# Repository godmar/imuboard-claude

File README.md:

# LSM6DSV32X Breakout

A minimal breakout for the ST **LSM6DSV32X** 6-axis IMU (±32 g accel, ±4000 dps gyro).
The circuit follows the mode 1 connection diagram in ST's datasheet (DS13511, Figure 28,
section 7.1).

| | |
|---|---|
| Board size | **20.32 × 10.2 mm**, 2 layers, 1.6 mm FR4. The width is set by the 8-pin header; the height meets JLCPCB's 10 × 10 mm minimum for assembly. |
| Mounting | Two M2 holes (2.2 mm, non-plated) in the top corners, 15.72 mm apart, 1.9 mm from the top edge. There is no copper within 2 mm of each hole, so a screw head or washer can't short anything. |
| Supply | 3.3 V only. VDD and VDDIO are tied together; there is no regulator or level shifter. |
| Interface | I²C / I3C (default) or SPI (3/4-wire) |
| I²C address | **0x6B** (SA0 pulled up by R3). Drive SDO low for 0x6A. |
| Parts | All SMD on top (0402 passives). The header is inserted from the bottom, so its plastic spacer sits under the board. |

## Header pinout (J1, 2.54 mm, pin 1 = square pad, left when viewed from the top)

| Pin | 1 | 2 | 3 | 4 | 5 | 6 | 7 | 8 |
|---|---|---|---|---|---|---|---|---|
| Signal | 3V3 | GND | INT2 | CS | SCL / SPC | SDA / SDI | SDO / SA0 | INT1 |

The order follows the ring of IMU pads, so every signal is routed on the top layer without
crossings. The pin names are printed on the back silkscreen.

## Circuit notes

- C1 / C2: 100 nF ceramic on VDDIO and VDD, placed next to the supply pins (datasheet Table 2 note 2, section 7.1).
- C3: 4.7 µF footprint on 3V3; may help if the board is fed through long wires or from a noisy robot supply. 
- R1 / R2: 10 k pull-ups on SCL / SDA (R<sub>pu</sub> = 10 kΩ per Figure 28), enabled through **JP1**, a solder jumper that is bridged by
  default. Cut the trace between its pads to remove the pull-ups, for example when the bus already
  has pull-ups or when using SPI.
- R3: 10 k pull-up on SDO/SA0. The SA0 pin has no internal pull-up by default, so without R3 the
  I²C address would be undefined. In SPI mode SDO actively drives the line, so R3 does no harm.
- CS has an internal pull-up, so the part starts in I²C/I3C mode. Pull CS low to use SPI.
- SDx/SCx (pins 2/3) are tied to GND because the analog hub, Qvar and sensor hub are not used.
  OCS_Aux/SDO_Aux (pins 10/11) are left unconnected. Both follow the datasheet's pin table.
- Axes: U1 is rotated 180° on the board. The front silkscreen arrow shows +X pointing left and
  +Y pointing toward the header; +Z points out of the top face.

## Files

| File | Contents |
|---|---|
| `lsm6dsv32x_breakout.kicad_pro/.kicad_sch/.kicad_pcb` | KiCad 9 project |
| `imuboard.kicad_sym`, `sym-lib-table` | Project symbol library (LSM6DSV32X symbol) |
| `fab/lsm6dsv32x_breakout_gerbers.zip` | Gerbers + Excellon drill files, ready to upload |
| `fab/*_bom.csv`, `fab/*_pos_top.csv` | BOM and top-side pick-and-place file (origin: bottom-left corner) |
| `fab/*_bom_jlcpcb.xlsx`, `fab/*_cpl_jlcpcb.xlsx` (+ `.csv`) | The same in JLCPCB's assembly upload format, matching their sample files (SMD parts only; J1 is fitted by hand) |
| `fab/*_schematic.pdf`, `fab/*_assembly_top.pdf` | Printable schematic and assembly drawing |
| `fab/erc.rpt`, `fab/drc.rpt` | Check reports (0 ERC, 0 DRC, 0 unconnected, 0 schematic-parity issues) |
| `tools/` | Generator scripts that produce the files above |

The design is **generated from scripts**. `tools/design.py` holds the netlist,
`tools/gen_schematic.py` writes the schematic, and `tools/gen_pcb.py` does placement,
routing, the GND pours on both layers, and the silkscreen. To rebuild everything, including
the fab outputs and the checks:

```sh
./tools/make_fab.sh
```

You can also edit the `.kicad_sch` / `.kicad_pcb` files directly in KiCad. Regenerating
overwrites those edits.

## Fabrication rules used

- Clearance 0.15 mm (the LGA's 0.5 mm pitch pads are 0.15 mm apart)
- Tracks 0.2 mm for signals, 0.3 mm for 3V3
- Vias 0.5 mm diameter / 0.3 mm drill, tented
- Copper to board edge 0.25 mm
- Copper keepout of 2 mm radius around each mounting hole

These are within standard JLCPCB/PCBWay 2-layer capabilities. The LGA-14 needs stencil and
reflow (or hot air) assembly.

The library footprints' silkscreen was moved to the Fab layers because the board is too dense
for it. For the same reason the project ignores the "footprint differs from library" DRC check.

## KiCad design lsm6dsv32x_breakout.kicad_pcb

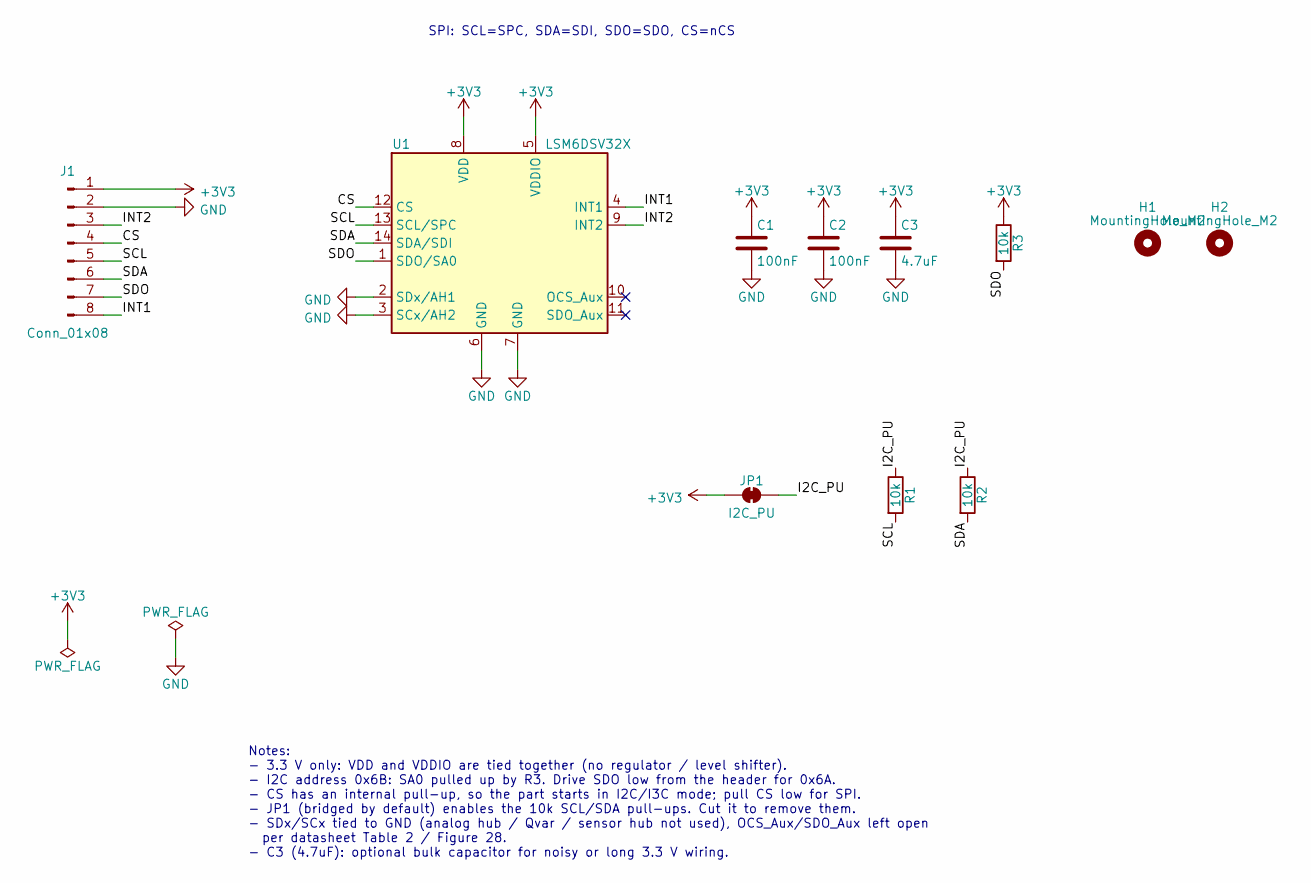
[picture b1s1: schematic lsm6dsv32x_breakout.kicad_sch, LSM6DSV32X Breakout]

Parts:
C1, C2: 100nF; C_0402_1005Metric
C3: 4.7uF; C_0402_1005Metric
H1, H2: MountingHole_M2; MountingHole_2.2mm_M2
J1: Conn_01x08; PinHeader_1x08_P2.54mm_Vertical
JP1: I2C_PU; SolderJumper-2_P1.3mm_Bridged_RoundedPad1.0x1.5mm
R1, R2, R3: 10k; R_0402_1005Metric
U1: LSM6DSV32X; LGA-14_3x2.5mm_P0.5mm_LayoutBorder3x4y; MPN LSM6DSV32XTR

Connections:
+3V3: C1.1, C2.1, C3.1, J1.1, JP1.1 (A), R3.1, U1.5 (VDDIO), U1.8 (VDD)
/CS: J1.4, U1.12 (CS)
/I2C_PU: JP1.2 (B), R1.1, R2.1
/INT1: J1.8, U1.4 (INT1)
/INT2: J1.3, U1.9 (INT2)
/SCL: J1.5, R1.2, U1.13 (SCL/SPC)
/SDA: J1.6, R2.2, U1.14 (SDA/SDI)
/SDO: J1.7, R3.2, U1.1 (SDO/SA0)
GND: C1.2, C2.2, C3.2, J1.2, U1.2 (SDx/AH1), U1.3 (SCx/AH2), U1.6 (GND), U1.7 (GND)

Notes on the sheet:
Notes: - 3.3 V only: VDD and VDDIO are tied together (no regulator / level shifter). - I2C address 0x6B: SA0 pulled up by R3. Drive SDO low from the header for 0x6A. - CS has an internal pull-up, so the part starts in I2C/I3C mode; pull CS low for SPI. - JP1 (bridged by default) enables the 10k SCL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
SPI: SCL=SPC, SDA=SDI, SDO=SDO, CS=nCS

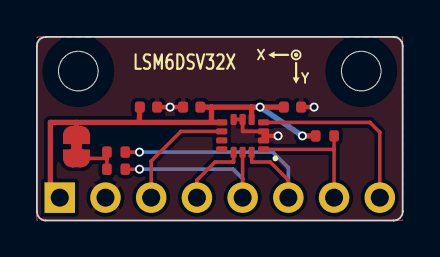
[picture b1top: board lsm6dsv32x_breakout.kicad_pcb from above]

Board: 2 copper layers, 20.3 x 10.2 mm, 11 parts (1 on the bottom side), 9 nets.

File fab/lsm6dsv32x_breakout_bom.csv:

"Refs","Value","Footprint","MPN","Note","Qty"
"C1,C2","100nF","Capacitor_SMD:C_0402_1005Metric","","Vdd decoupling,Vdd_IO decoupling","2"
"C3","4.7uF","Capacitor_SMD:C_0402_1005Metric","","optional bulk for noisy/long supply wiring, X5R 6.3V+","1"
"J1","Conn_01x08","Connector_PinHeader_2.54mm:PinHeader_1x08_P2.54mm_Vertical","","","1"
"R1-R3","10k","Resistor_SMD:R_0402_1005Metric","","SA0=1 -> I2C addr 0x6B","3"
"U1","LSM6DSV32X","Package_LGA:LGA-14_3x2.5mm_P0.5mm_LayoutBorder3x4y","LSM6DSV32XTR","","1"

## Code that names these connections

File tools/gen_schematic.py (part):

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        pin('input', '12', 'CS', -17.78, 5.08, 0),
        pin('input', '13', 'SCL/SPC', -17.78, 2.54, 0),
        pin('bidirectional', '14', 'SDA/SDI', -17.78, 0, 0),
        pin('bidirectional', '1', 'SDO/SA0', -17.78, -2.54, 0),
        pin('passive', '2', 'SDx/AH1', -17.78, -7.62, 0),
        pin('passive', '3', 'SCx/AH2', -17.78, -10.16, 0),
        pin('output', '4', 'INT1', 17.78, 5.08, 180),
        pin('output', '9', 'INT2', 17.78, 2.54, 180),
        pin('passive', '10', 'OCS_Aux', 17.78, -7.62, 180),
        pin('passive', '11', 'SDO_Aux', 17.78, -10.16, 180),
        pin('power_in', '8', 'VDD', -5.08, 15.24, 270),
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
